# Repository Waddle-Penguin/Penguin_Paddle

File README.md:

# Penguin Paddle!

**Design Time: ~21 Hours**
**Build Time: ~5 Hours**

**Total Time: ~26 Hours:**

Hi everybody, this is the project I've been working on recently for Hackclub's Undercity. 

Penguin Paddle is my own touch-sensitive iambic morse code keyer that has multiple differrent output options, including a buzzer to make sound. It is designed with future expansion in mind with mounting holes and solder joints for potentially adding vertical pads in the future (Which will be printed as a snap-off section of my PCB), as well as a usb-c port for keyboard support. 

It uses two switches and two potentiometers to control all of the settings from on the board, so there is no challenge when trying to increase the speed of your keying or vice versa. It uses a piezo buzzer to make the sound and the volume is adjustable, and it has an overall On/Off switch. 

I decided to make it because I've ben getting into morse code, and I had an idea a while beck to create my own keyer as I don't have one, so when I realized I needed to make a project for Highway to Undercity that would have grants for my hardware I was exited to realize this was the perfect oppurtunity to create it! Hopefully it should help me do what I am trying to do with morse code; connecting and sharing stories with people across the world with my own unique twist.

Schematic Photos

PCB Photos:

Case Photos:

# BOM

| Quantity | Part | Link | Price |
| ----------- | ----------- |----------- |----------- |
| 1 | 3.5mm Stereo Audio Jack | https://www.digikey.ca/en/products/detail/same-sky-formerly-cui-devices/SJ1-3533NG/738701 | $1.82 |
| 2 | 10k Rotatary Potentiometer | https://www.digikey.ca/en/products/detail/tt-electronics-bi/P0915N-EC15BR10K/4780755 | $6.68 |
| 1 | 12.2mm Piezo Buzzer | https://www.digikey.ca/en/products/detail/tdk-corporation/PS1240P02BT/935924 | $0.84 |
| 1 | Xiao ESP32-S3 | https://www.digikey.ca/en/products/detail/seeed-technology-co-ltd/113991114/19285530 | $11.63 |
| 2 | 30v SPDT Slide Switch | https://www.digikey.ca/en/products/detail/c-k/SS-12D07-VG-4-NS-GA-PA/2747177 | $2.73 |
| 1 | 1k Axial Resistor | https://www.digikey.ca/en/products/detail/stackpole-electronics-inc/CF14JT1K00/1741314 | $0.32 |
| 1 | 45v NPN Transistor | https://www.digikey.ca/en/products/detail/onsemi/BC550CBU/975565 | $0.45 |
| 4 (1 Set) | Slicone Non-slip feet | https://www.digikey.ca/en/products/detail/sparkfun-electronics/17736/13629023 | $1.63 |
| 1 | Custom PCB | For me: https://cart.jlcpcb.com/shopcart/cart |  $2.84 + $2.03 Shipping |

+ $8 Digikey Shipping
# Total: ~$34 CAD / $25.05 USD

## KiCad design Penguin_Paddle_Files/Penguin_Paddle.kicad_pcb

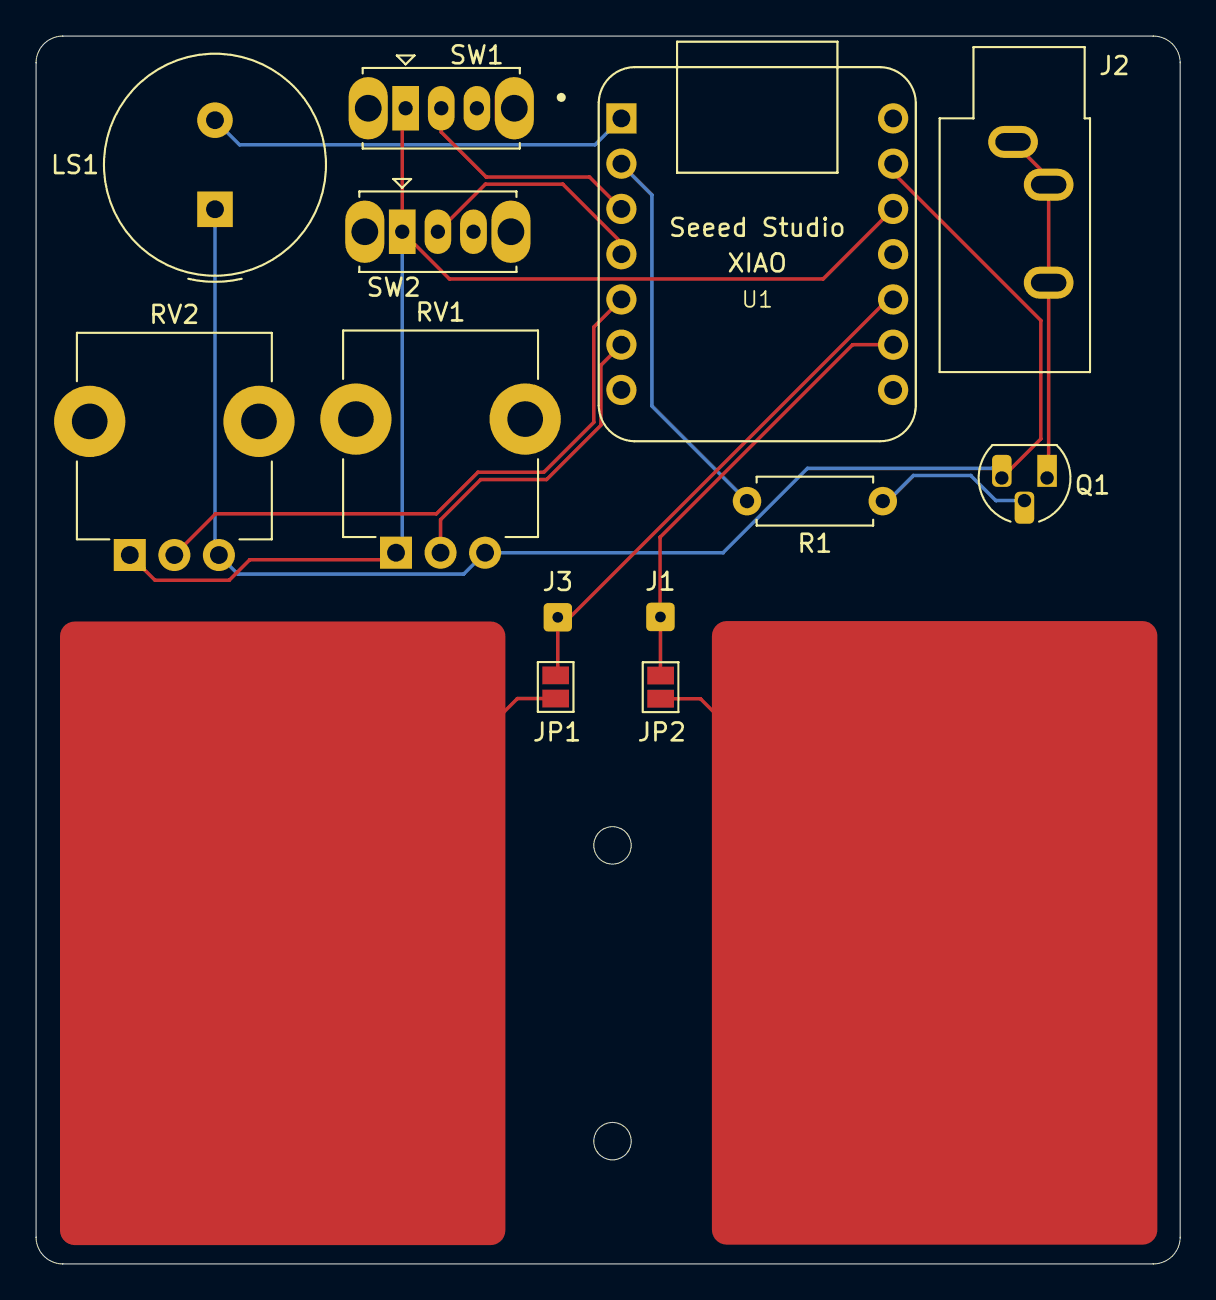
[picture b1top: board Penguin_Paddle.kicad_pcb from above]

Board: 2 copper layers, 64.2 x 68.9 mm, 15 parts (0 on the bottom side), 14 nets.

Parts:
J1, J3: Conn_01x01_Socket; SolderWire-0.1sqmm_1x01_D0.4mm_OD1mm
J2: AudioPlug3; Jack_3.5mm_CUI_SJ1-3533NG_Horizontal
JP1, JP2: SolderJumper_2_Open; SolderJumper-2_P1.3mm_Open_Pad1.0x1.5mm
LS1: PS1240P02BT; Buzzer_TDK_PS1240P02BT_D12.2mm_H6.5mm
Q1: NPN; TO-92L_HandSolder
R1: 1k; R_Axial_DIN0207_L6.3mm_D2.5mm_P7.62mm_Horizontal
RV1, RV2: R_Potentiometer; Potentiometer_TT_P0915N
SW1, SW2: SW_SPST; SW_Slide_SPDT_Straight_CK_OS102011MS2Q
TP1, TP2: TestPoint; Copper Pad
U1: XIAO-ESP32-S3-DIP; XIAO-Generic-Thruhole-14P-2.54-21X17.8MM

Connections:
+3V3: RV1.1, RV2.1, SW1.1 (A), SW2.1 (A), U1.12 (VCC_3V3)
GND: LS1.1, Q1.3 (E), RV1.3, RV2.3, U1.13 (GND)
unnamed: J1.1, JP2.1 (A), U1.9 (GPIO7/D8/A8/SCK)
unnamed: J3.1, JP1.1 (A), U1.10 (GPIO8/D9/A9/MISO)
unnamed: JP1.2 (B), TP2.1
unnamed: JP2.2 (B), TP1.1
unnamed: Q1.2 (B), R1.1
unnamed: J2.R, J2.S, J2.T, Q1.1 (C)
unnamed: SW1.2 (B), U1.3 (GPIO3/D2/A2)
unnamed: SW2.2 (B), U1.4 (GPIO4/D3/A3)
unnamed: LS1.2, U1.1 (GPIO1/D0/A0)
unnamed: R1.2, U1.2 (GPIO2/DA/A1)
unnamed: RV2.2, U1.5 (GPIO5/D4/I2C_SDA)
unnamed: RV1.2, U1.6 (GPIO9/D5/I2C_SCL)

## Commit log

2025-06-28 Journal Log June 27/28th
2025-06-28 Minor Journal Edits
2025-06-28 Can I get rid of these?
2025-06-28 No I Cannot
2025-06-28 I have now learned not to mess with git
2025-06-28 I think this should fix everything
2025-06-28 18 Millionth try lucky? (I just want to sleep)
2025-06-28 Journal Entry June 28th
2025-06-28 Small change
2025-06-30 Journal Entry June 29th
2025-06-30 Began README Framework
2025-07-01 test
2025-07-01 Added BOM, started (kinda) README
2025-07-01 Journal Entry June 30th
2025-07-01 Added Photo
2025-07-02 Updated .scv BOM
2025-07-02 Created software: 1.0
2025-07-02 what is going on
2025-07-02 Now Can I do this?
2025-07-02 Journal Entry July 1st (Happy Canada Day!)
2025-07-02 Update README.md on phone
2025-07-03 README Complete?
2025-07-03 Journal Entry July 2nd
2025-07-03 Almost Done!
2025-07-04 Update BOM
2025-07-05 Cleaned folders (frogot to commit this a few days ago)
2025-07-07 Updated mousebites
2025-08-06 Finished Code, Switched to Mircopython, updated Gerbers
2025-08-06 Update Build Time
2025-08-06 Journal Entry August 1st - 2nd
